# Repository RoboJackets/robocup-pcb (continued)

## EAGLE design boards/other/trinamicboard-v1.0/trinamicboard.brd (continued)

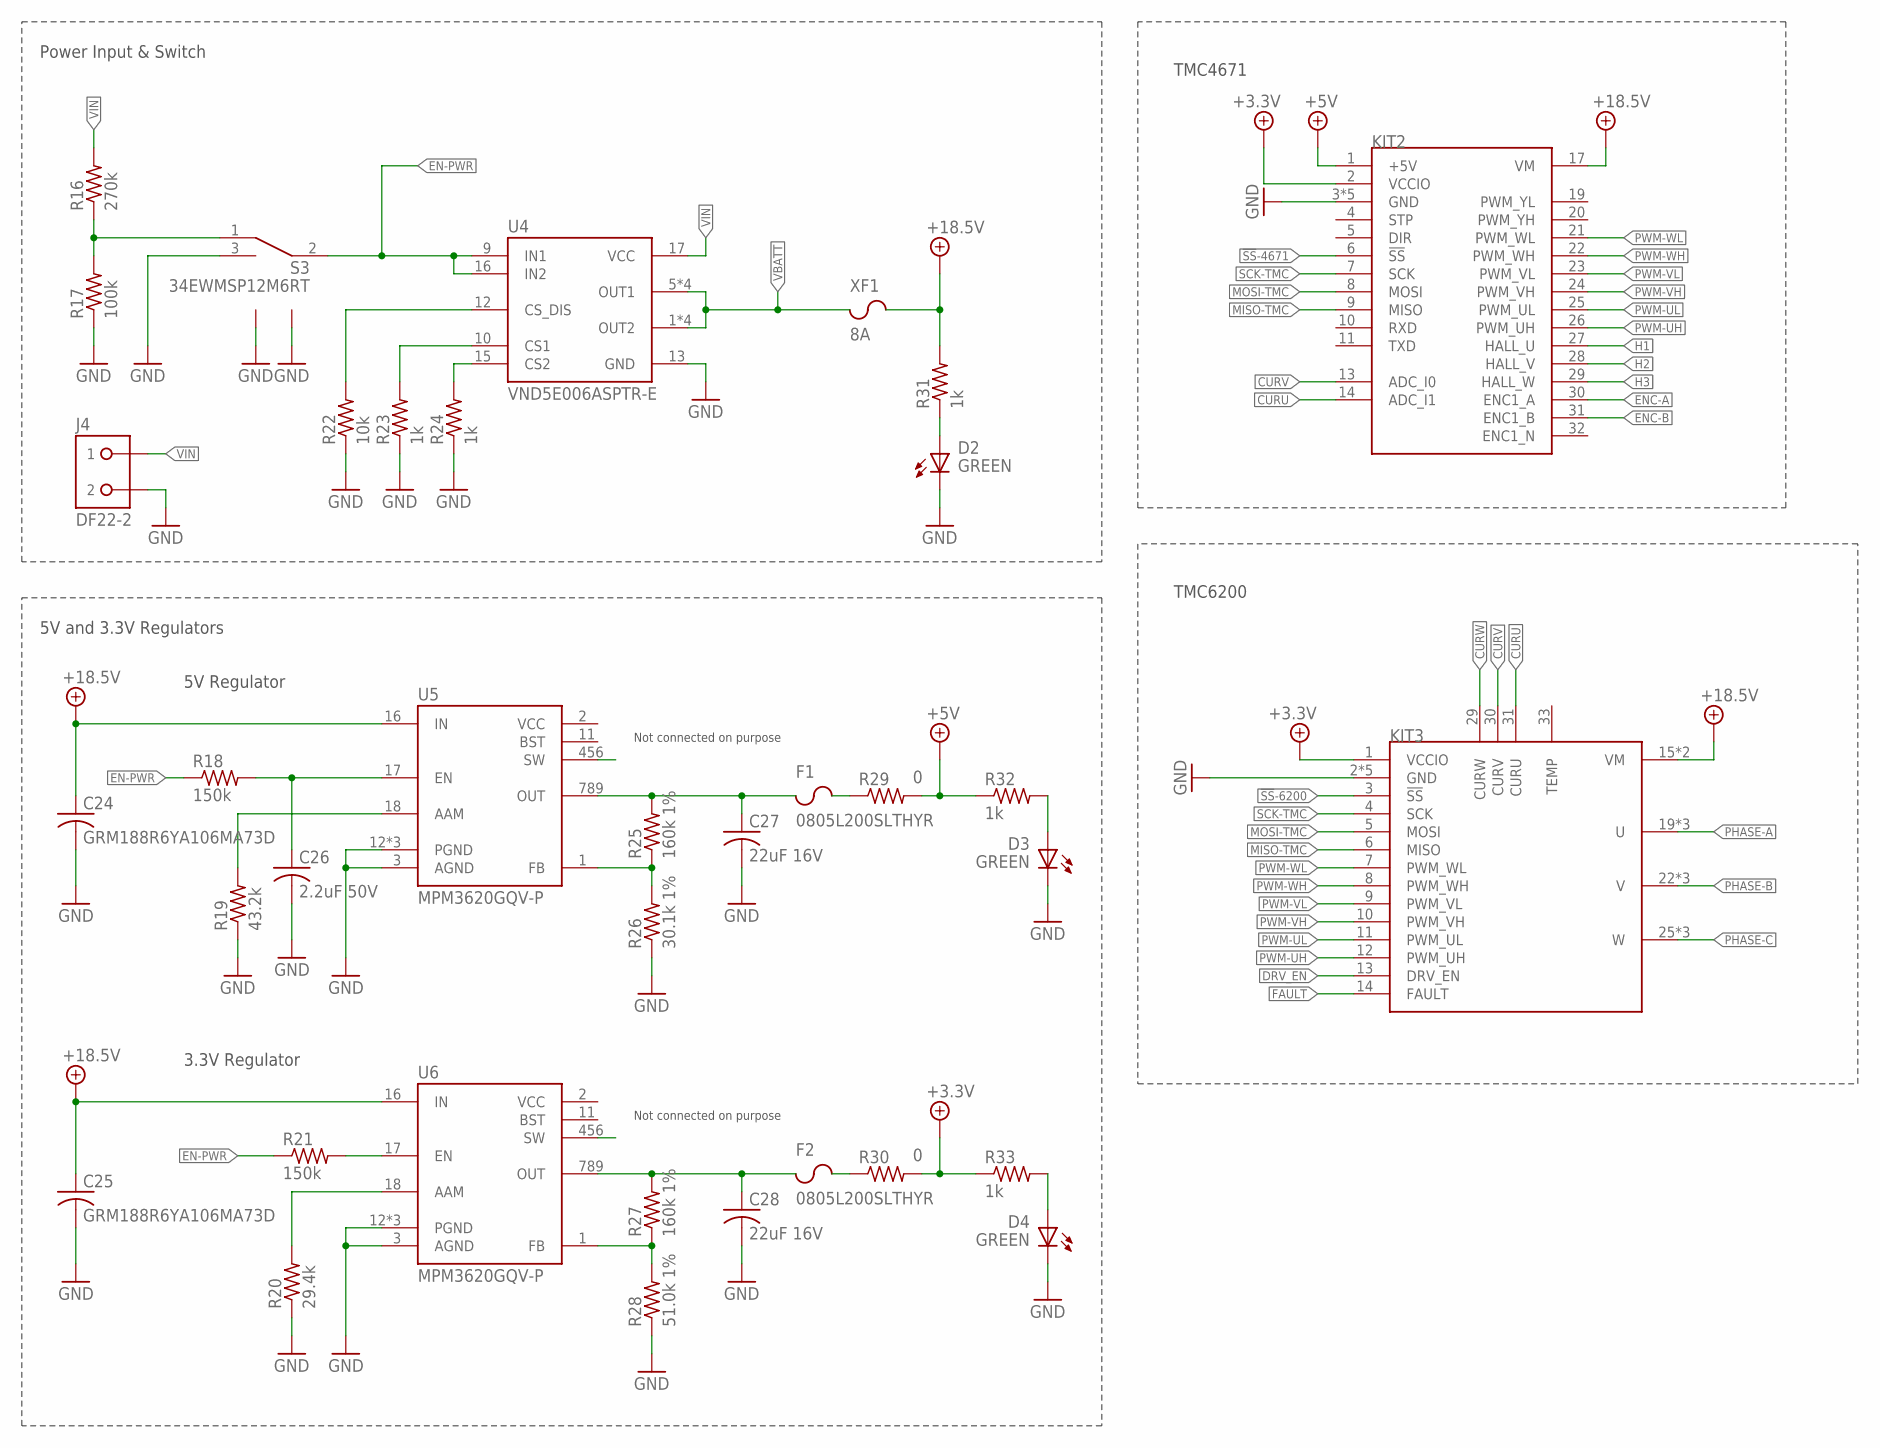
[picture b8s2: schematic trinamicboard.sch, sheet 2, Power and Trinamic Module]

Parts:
C24, C25: GRM188R6YA106MA73D; C0603
C26: 2.2uF 50V; C0603
C27, C28: 22uF 16V; C0805
D2, D3, D4: GREEN; CHIP-LED0603
F1, F2: 0805L200SLTHYR; FUSC2113X75
J4: DF22-2; DF22-2-H
KIT2: TMC4671-BOB
KIT3: TMC6200-BOB
R16: 270k; R0603
R17: 100k; R0603
R18, R21: 150k; R0603
R19: 43.2k; R0603
R20: 29.4k; R0603
R22: 10k; R0603
R23, R24, R31, R32, R33: 1k; R0603
R25, R27: 160k 1%; R0603
R26: 30.1k 1%; R0603
R28: 51.0k 1%; R0603
R29, R30: 0; R0603
S3: 34EWMSP12M6RT
U4: VND5E006ASPTR-E; POWERSO-16
U5, U6: MPM3620GQV-P; MPN MPM3620GQV-P; DIGIKEY 1589-1252-1-ND
XF1: 8A; 3557-2

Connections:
2+5V: KIT2.1 (+5V), R29.2, R32.1; also elsewhere on the board
18.5V-LED: D2.A, R31.1
!SS!-4671: KIT2.6 (!SS!); also elsewhere on the board
!SS!-6200: KIT3.3 (!SS!); also elsewhere on the board
+3.3V: KIT2.2 (VCCIO), KIT3.1 (VCCIO), R30.2, R33.1; also elsewhere on the board
+3.3V-FUSE: C28.1, F2.1, R27.2, U6.789 (OUT)
+3.3V-LED: D4.A, R33.2
+3.3V-PREFUSE: F2.2, R30.1
+5V-FUSE: C27.1, F1.1, R25.2, U5.789 (OUT)
+5V-LED: D3.A, R32.2
+5V-PREFUSE: F1.2, R29.1
+18.5V: C24.1, C25.1, KIT2.17 (VM), KIT3.15 (VM), KIT3.16 (VM), R31.2, U5.16 (IN), U6.16 (IN), XF1.3 (2), XF1.4 (2); also elsewhere on the board
AAM: R19.2, U5.18 (AAM)
AAM1: R20.2, U6.18 (AAM)
CS1: R23.2, U4.10 (CS1)
CS2: R24.2, U4.15 (CS2)
CS-DIS: R22.2, U4.12 (CS_DIS)
CURU: KIT2.14 (ADC_I1), KIT3.31 (CURU); also elsewhere on the board
CURV: KIT2.13 (ADC_I0), KIT3.30 (CURV); also elsewhere on the board
CURW: KIT3.29 (CURW); also elsewhere on the board
DRV_EN: KIT3.13 (DRV_EN); also elsewhere on the board
EN: C26.1, R18.2, U5.17 (EN)
EN1: R21.2, U6.17 (EN)
EN-PWR: R18.1, R21.1, S3.2 (COMMON), U4.9 (IN1), U4.16 (IN2)
EN-PWR-PRE: R16.1, R17.2, S3.1 (A)
ENC-A: KIT2.30 (ENC1_A); also elsewhere on the board
ENC-B: KIT2.31 (ENC1_B); also elsewhere on the board
FAULT: KIT3.14 (FAULT); also elsewhere on the board
FB: R25.1, R26.2, U5.1 (FB)
FB1: R27.1, R28.2, U6.1 (FB)
GND: C24.2, C25.2, C26.2, C27.2, C28.2, D2.C (K), D3.C (K), D4.C (K), J4.2, KIT2.3 (GND), KIT2.12 (GND), KIT2.15 (GND), KIT2.16 (GND), KIT2.18 (GND), KIT3.2 (GND), KIT3.17 (GND), KIT3.18 (GND), KIT3.28 (GND), KIT3.32 (GND), R17.1, R19.1, R20.1, R22.1, R23.1, R24.1, R26.1, R28.1, S3.3 (B), S3.LEG1, S3.LEG3 (LEG2), U4.13 (GND), U5.3 (AGND), U5.12 (PGND), U5.13 (PGND), U5.14 (PGND), U6.3 (AGND), U6.12 (PGND), U6.13 (PGND), U6.14 (PGND); also elsewhere on the board
H1: KIT2.27 (HALL_U); also elsewhere on the board
H2: KIT2.28 (HALL_V); also elsewhere on the board
H3: KIT2.29 (HALL_W); also elsewhere on the board
MISO-TMC: KIT2.9 (MISO), KIT3.6 (MISO); also elsewhere on the board
MOSI-TMC: KIT2.8 (MOSI), KIT3.5 (MOSI); also elsewhere on the board
PHASE-A: KIT3.19 (U), KIT3.20 (U), KIT3.21 (U); also elsewhere on the board
PHASE-B: KIT3.22 (V), KIT3.23 (V), KIT3.24 (V); also elsewhere on the board
PHASE-C: KIT3.25 (W), KIT3.26 (W), KIT3.27 (W); also elsewhere on the board
PWM-UH: KIT2.26 (PWM_UH), KIT3.12 (PWM_UH); also elsewhere on the board
PWM-UL: KIT2.25 (PWM_UL), KIT3.11 (PWM_UL); also elsewhere on the board
PWM-VH: KIT2.24 (PWM_VH), KIT3.10 (PWM_VH); also elsewhere on the board
PWM-VL: KIT2.23 (PWM_VL), KIT3.9 (PWM_VL); also elsewhere on the board
PWM-WH: KIT2.22 (PWM_WH), KIT3.8 (PWM_WH); also elsewhere on the board
PWM-WL: KIT2.21 (PWM_WL), KIT3.7 (PWM_WL); also elsewhere on the board
SCK-TMC: KIT2.7 (SCK), KIT3.4 (SCK); also elsewhere on the board
SW: U5.456 (SW)
SW1: U6.456 (SW)
VBATT: U4.1 (OUT2), U4.2 (OUT2), U4.3 (OUT2), U4.4 (OUT2), U4.5 (OUT1), U4.6 (OUT1), U4.7 (OUT1), U4.8 (OUT1), XF1.1, XF1.2 (1)
VIN: J4.1, R16.2, U4.17 (VCC)

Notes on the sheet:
Power Input & Switch
5V and 3.3V Regulators
Not connected on purpose
5V Regulator
3.3V Regulator
TMC4671
TMC6200

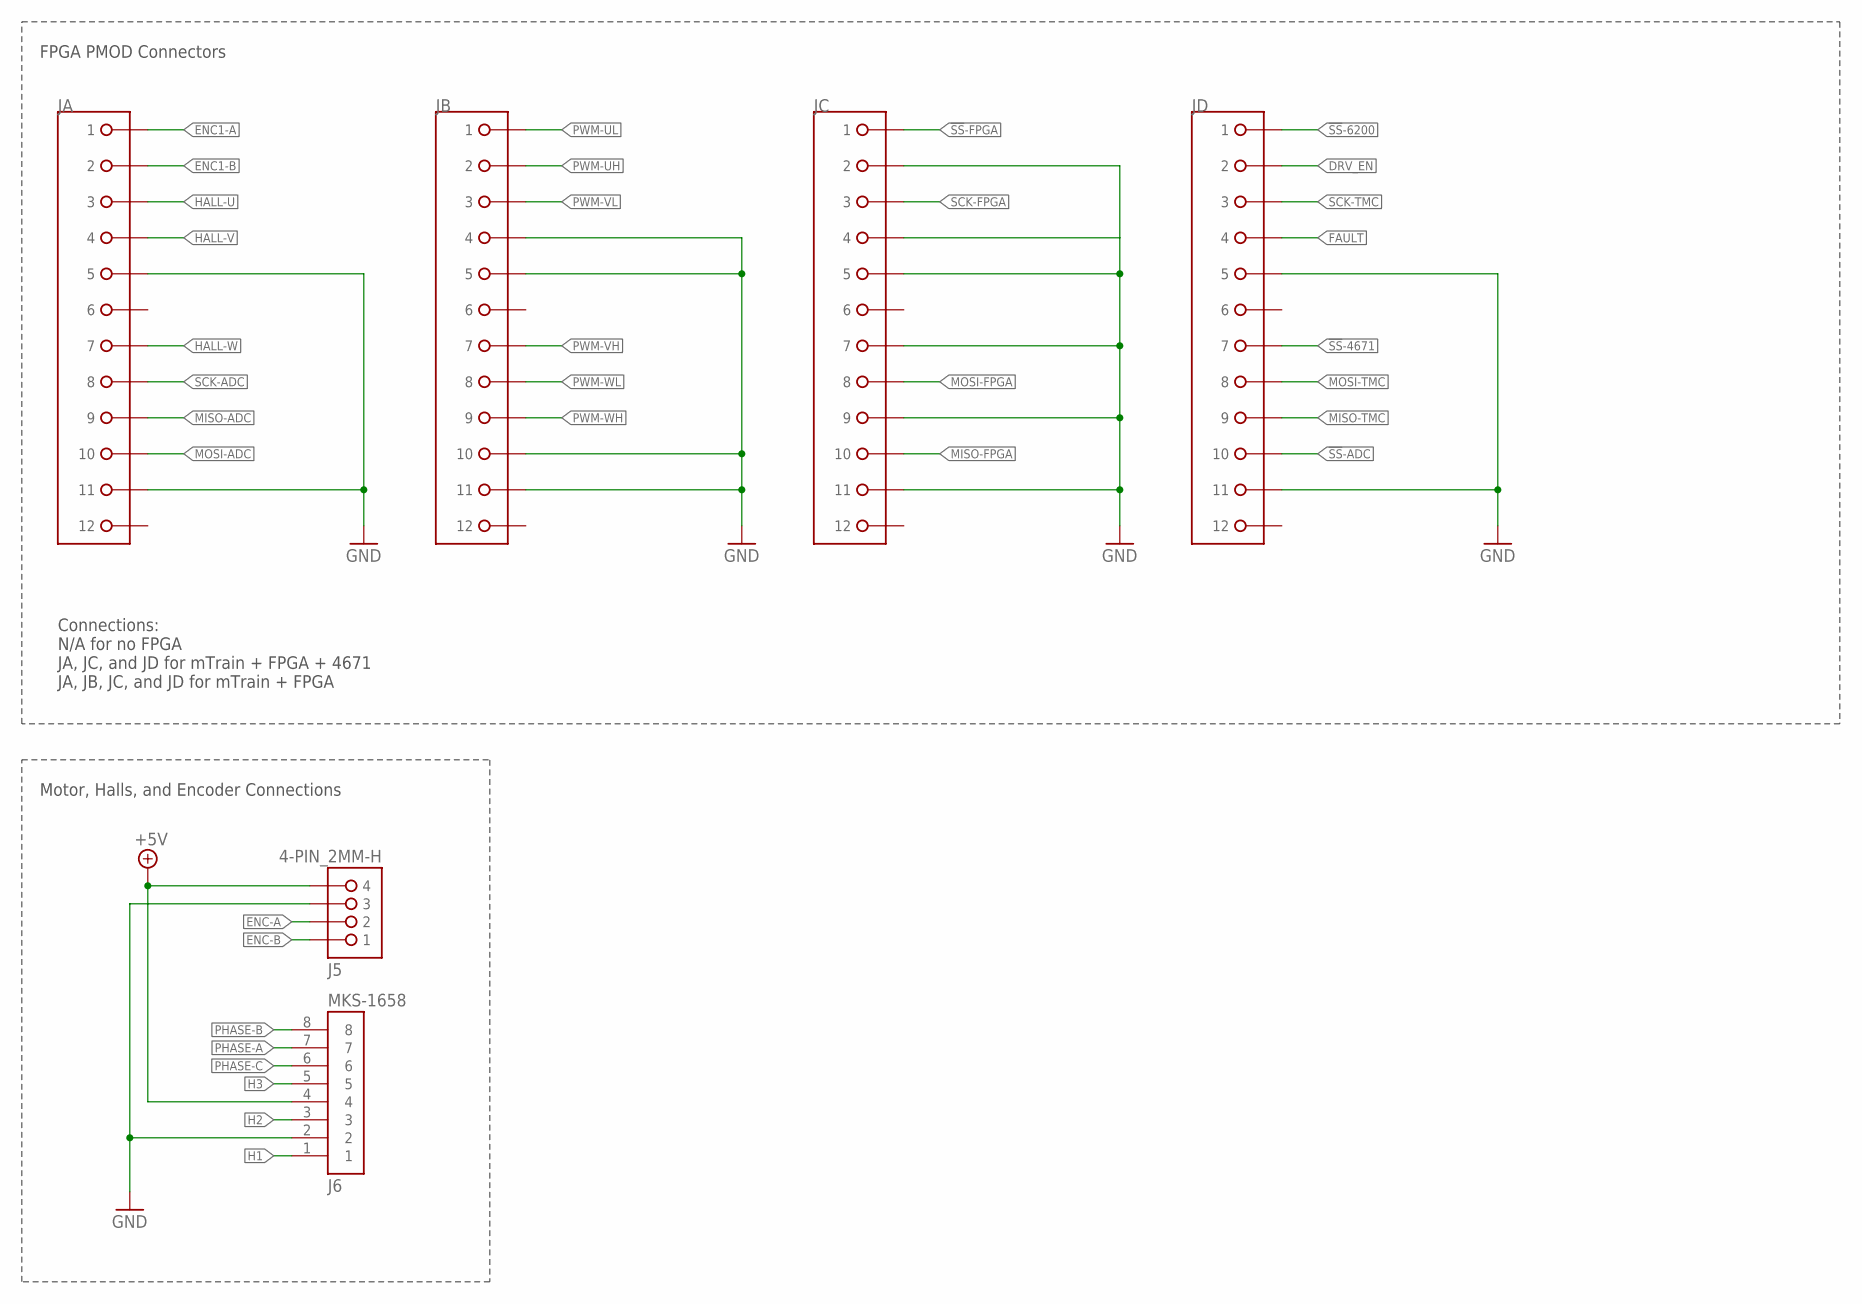
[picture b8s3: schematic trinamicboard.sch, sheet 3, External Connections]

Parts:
J5: 4-PIN_2MM-H; 2MM-4-H
J6: MKS-1658
JA: PMOD
JB: PMOD
JC: PMOD
JD: PMOD

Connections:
2+5V: J5.4, J6.4; also elsewhere on the board
!SS!-4671: JD.1 (7); also elsewhere on the board
!SS!-6200: JD.7 (1); also elsewhere on the board
!SS!-ADC: JD.4 (10); also elsewhere on the board
!SS!-FPGA: JC.7 (1); also elsewhere on the board
DRV_EN: JD.8 (2); also elsewhere on the board
ENC1-A: JA.7 (1); also elsewhere on the board
ENC1-B: JA.8 (2); also elsewhere on the board
ENC-A: J5.2; also elsewhere on the board
ENC-B: J5.1; also elsewhere on the board
FAULT: JD.10 (4); also elsewhere on the board
GND: J5.3, J6.2, JA.5 (11), JA.11 (5), JB.4 (10), JB.5 (11), JB.10 (4), JB.11 (5), JC.1 (7), JC.3 (9), JC.5 (11), JC.8 (2), JC.10 (4), JC.11 (5), JD.5 (11), JD.11 (5); also elsewhere on the board
H1: J6.1; also elsewhere on the board
H2: J6.3; also elsewhere on the board
H3: J6.5; also elsewhere on the board
HALL-U: JA.9 (3); also elsewhere on the board
HALL-V: JA.10 (4); also elsewhere on the board
HALL-W: JA.1 (7); also elsewhere on the board
MISO-ADC: JA.3 (9); also elsewhere on the board
MISO-FPGA: JC.4 (10)
MISO-TMC: JD.3 (9); also elsewhere on the board
MOSI-ADC: JA.4 (10); also elsewhere on the board
MOSI-FPGA: JC.2 (8); also elsewhere on the board
MOSI-TMC: JD.2 (8); also elsewhere on the board
PHASE-A: J6.7; also elsewhere on the board
PHASE-B: J6.8; also elsewhere on the board
PHASE-C: J6.6; also elsewhere on the board
PWM-UH: JB.8 (2); also elsewhere on the board
PWM-UL: JB.7 (1); also elsewhere on the board
PWM-VH: JB.1 (7); also elsewhere on the board
PWM-VL: JB.9 (3); also elsewhere on the board
PWM-WH: JB.3 (9); also elsewhere on the board
PWM-WL: JB.2 (8); also elsewhere on the board
SCK-ADC: JA.2 (8); also elsewhere on the board
SCK-FPGA: JC.9 (3); also elsewhere on the board
SCK-TMC: JD.9 (3); also elsewhere on the board

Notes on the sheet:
Motor, Halls, and Encoder Connections
FPGA PMOD Connectors
Connections: N/A for no FPGA JA, JC, and JD for mTrain + FPGA + 4671 JA, JB, JC, and JD for mTrain + FPGA

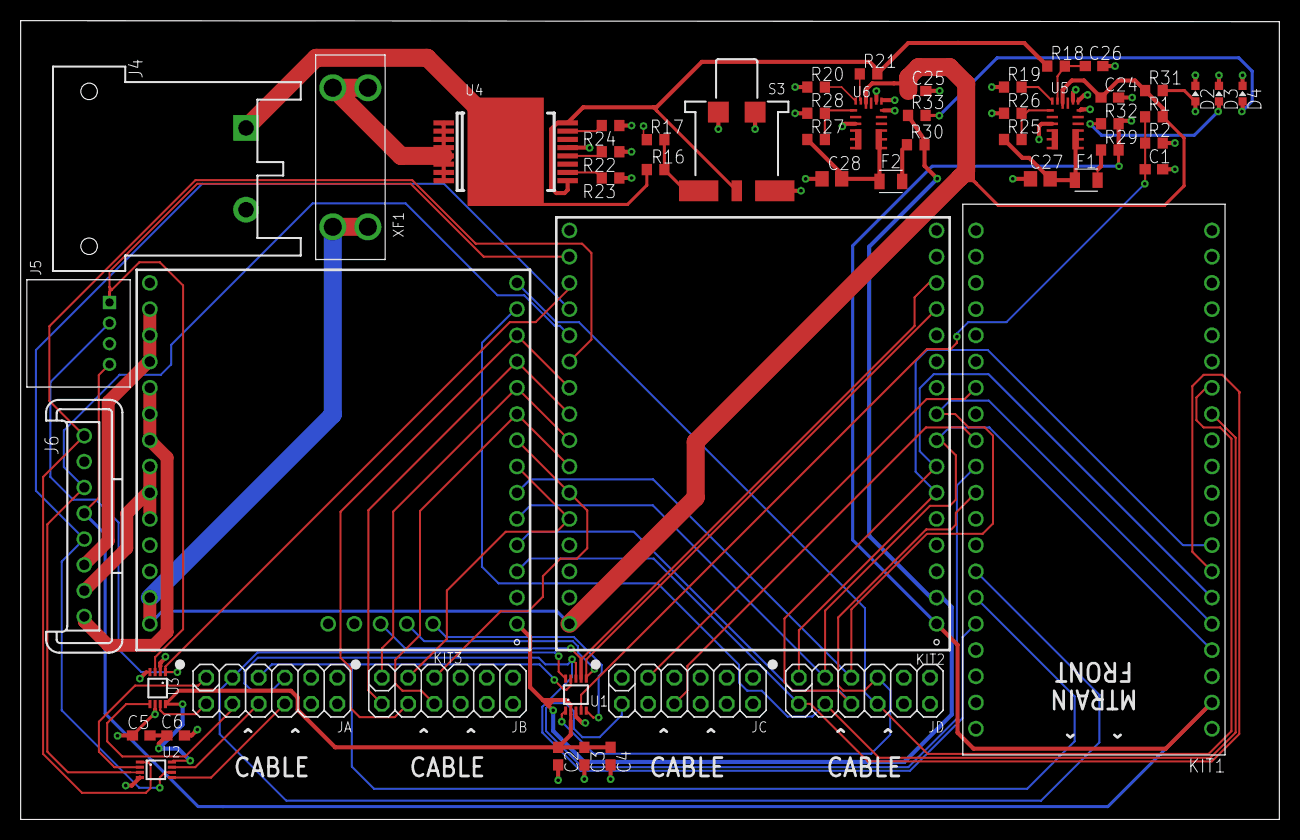
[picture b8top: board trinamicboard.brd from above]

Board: 2 copper layers, 121.9 x 77.4 mm, 54 parts (0 on the bottom side), 61 nets.
